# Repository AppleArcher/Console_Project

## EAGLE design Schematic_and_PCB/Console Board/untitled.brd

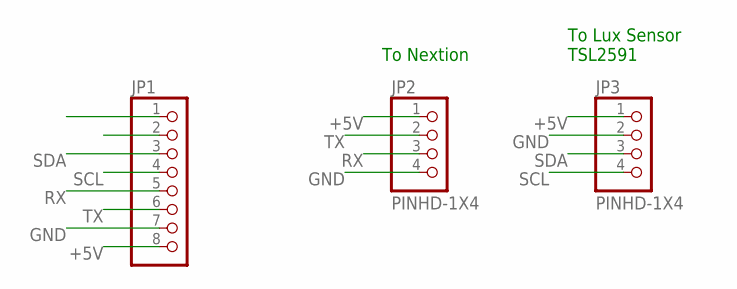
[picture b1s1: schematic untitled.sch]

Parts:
JP1: PINHD-1X8BIG; 1X08-BIG
JP2, JP3: PINHD-1X4; 1X04

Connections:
+5V: JP1.8, JP2.1, JP3.1
GND: JP1.7, JP2.4, JP3.2
RX: JP1.5, JP2.3
SCL: JP1.4, JP3.4
SDA: JP1.3, JP3.3
TX: JP1.6, JP2.2

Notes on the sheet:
To Nextion
To Lux Sensor TSL2591

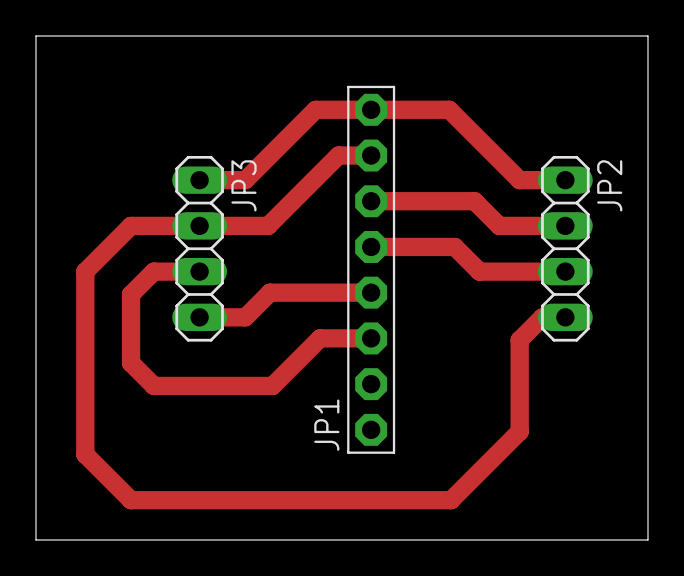
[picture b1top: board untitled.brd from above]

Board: 2 copper layers, 34.0 x 28.0 mm, 3 parts (0 on the bottom side), 6 nets.

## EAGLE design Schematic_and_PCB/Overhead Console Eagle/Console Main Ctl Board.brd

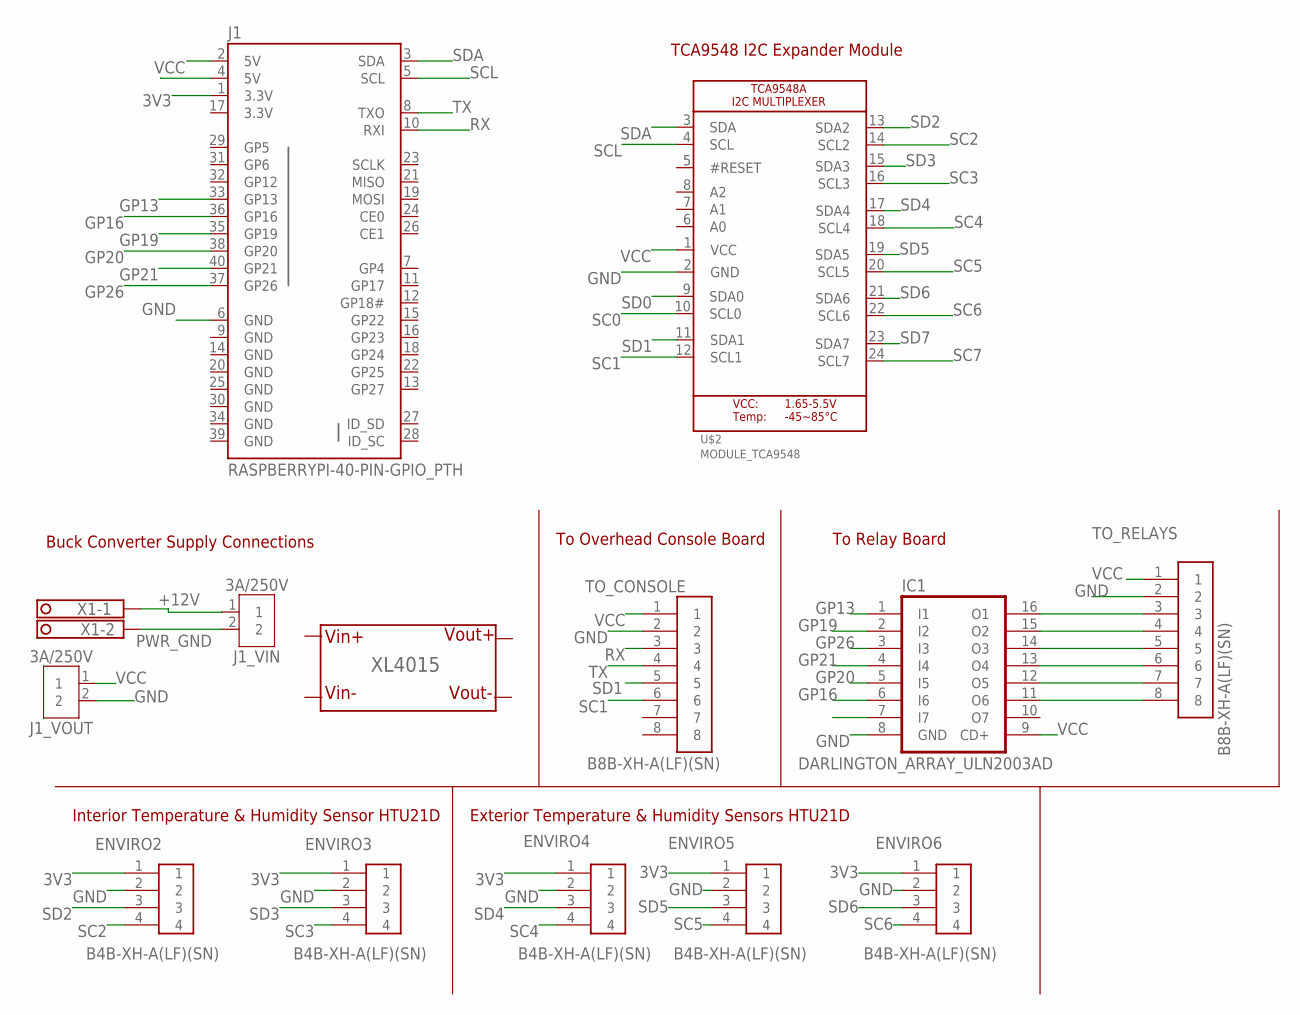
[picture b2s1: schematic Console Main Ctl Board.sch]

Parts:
ENVIRO2, ENVIRO3, ENVIRO4, ENVIRO5, ENVIRO6: B4B-XH-A(LF)(SN)
IC1: DARLINGTON_ARRAY_ULN2003AD; SO16
J1: RASPBERRYPI-40-PIN-GPIO_PTH; 2X20_SHROUDED
J1_VIN, J1_VOUT: 3A/250V; B2B-XH-A
TO_CONSOLE: B8B-XH-A(LF)(SN)
TO_RELAYS: B8B-XH-A(LF)(SN)
U$1: XL4015-MODULE
U$2: MODULE_TCA9548; MODULE_TCA9548A
X1: TERMINAL-BLOCK-3.5MM-2-PIN-LONG-PAD; TERMINAL-BLOCK-2-PIN-3.5MM-LONG-PAD

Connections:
3.3V: J1.17 (3.3V)
3V3: ENVIRO2.1, ENVIRO3.1, ENVIRO4.1, ENVIRO5.1, ENVIRO6.1, J1.1 (3.3V)
+12V: J1_VIN.1, X1.1
GND: ENVIRO2.2, ENVIRO3.2, ENVIRO4.2, ENVIRO5.2, ENVIRO6.2, IC1.8 (GND), J1.6 (GND), J1.9 (GND), J1.14 (GND), J1.20 (GND), J1.25 (GND), J1.30 (GND), J1.34 (GND), J1.39 (GND), J1_VOUT.2, TO_CONSOLE.2, TO_RELAYS.2, U$2.2 (GND)
GP13: IC1.1 (I1), J1.33 (GP13)
GP16: IC1.6 (I6), J1.36 (GP16)
GP19: IC1.2 (I2), J1.35 (GP19)
GP20: IC1.5 (I5), J1.38 (GP20)
GP21: IC1.4 (I4), J1.40 (GP21)
GP26: IC1.3 (I3), J1.37 (GP26)
unnamed: IC1.16 (O1), TO_RELAYS.3
unnamed: IC1.15 (O2), TO_RELAYS.4
unnamed: IC1.14 (O3), TO_RELAYS.5
unnamed: IC1.13 (O4), TO_RELAYS.6
unnamed: IC1.12 (O5), TO_RELAYS.7
unnamed: IC1.11 (O6), TO_RELAYS.8
PWR_GND: J1_VIN.2, X1.2
RX: J1.10 (RXI), TO_CONSOLE.3
SC0: U$2.10 (SCL0)
SC1: TO_CONSOLE.6, U$2.12 (SCL1)
SC2: ENVIRO2.4, U$2.14 (SCL2)
SC3: ENVIRO3.4, U$2.16 (SCL3)
SC4: ENVIRO4.4, U$2.18 (SCL4)
SC5: ENVIRO5.4, U$2.20 (SCL5)
SC6: ENVIRO6.4, U$2.22 (SCL6)
SC7: U$2.24 (SCL7)
SCL: J1.5 (SCL), U$2.4 (SCL)
SD0: U$2.9 (SDA0)
SD1: TO_CONSOLE.5, U$2.11 (SDA1)
SD2: ENVIRO2.3, U$2.13 (SDA2)
SD3: ENVIRO3.3, U$2.15 (SDA3)
SD4: ENVIRO4.3, U$2.17 (SDA4)
SD5: ENVIRO5.3, U$2.19 (SDA5)
SD6: ENVIRO6.3, U$2.21 (SDA6)
SD7: U$2.23 (SDA7)
SDA: J1.3 (SDA), U$2.3 (SDA)
TX: J1.8 (TXO), TO_CONSOLE.4
VCC: IC1.9 (CD+), J1.2 (5V), J1_VOUT.1, TO_CONSOLE.1, TO_RELAYS.1, U$2.1 (VCC)

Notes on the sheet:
To Overhead Console Board
To Relay Board
TCA9548 I2C Expander Module
Interior Temperature & Humidity Sensor HTU21D
Exterior Temperature & Humidity Sensors HTU21D
Buck Converter Supply Connections

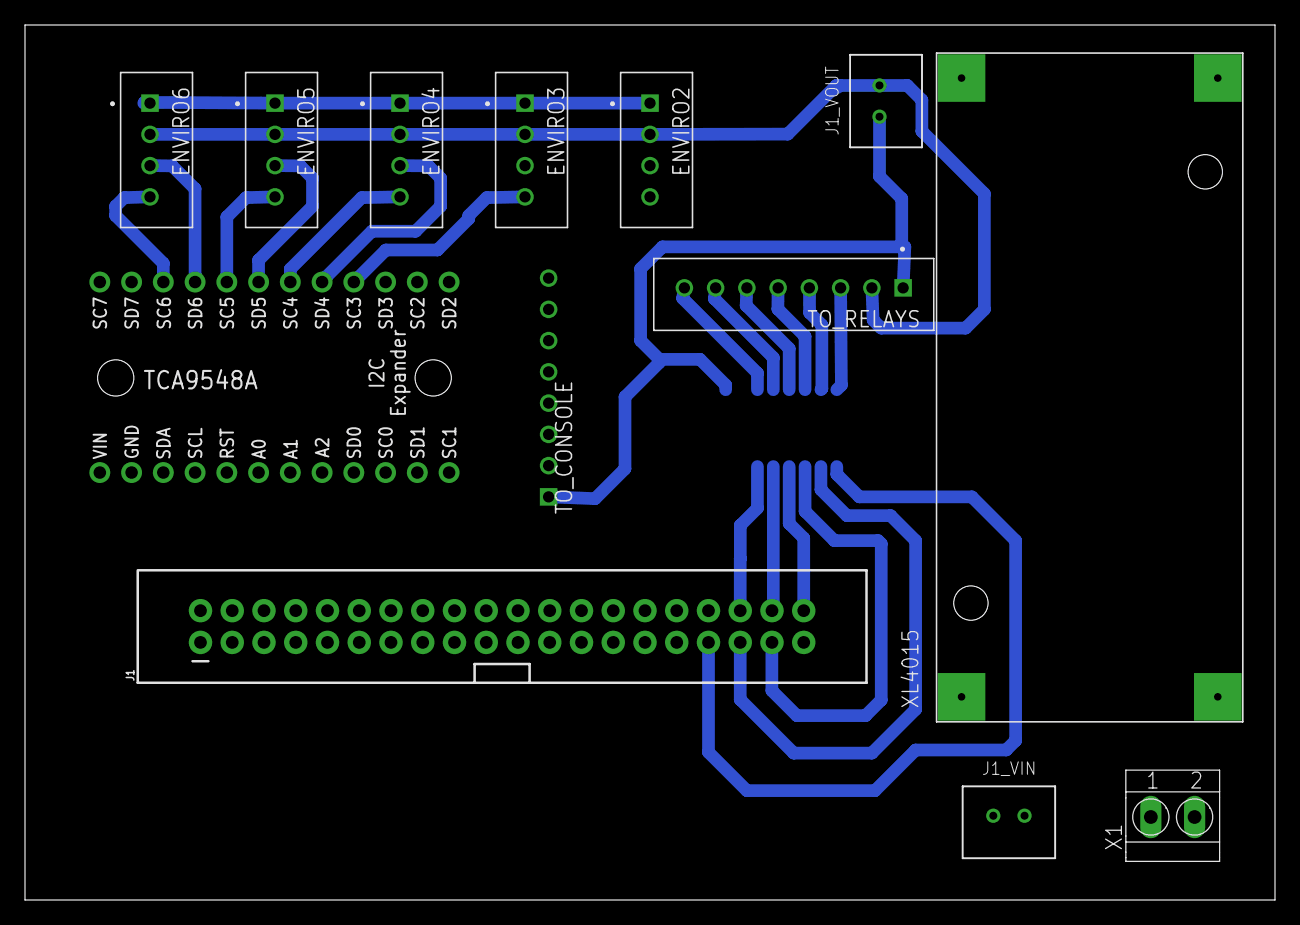
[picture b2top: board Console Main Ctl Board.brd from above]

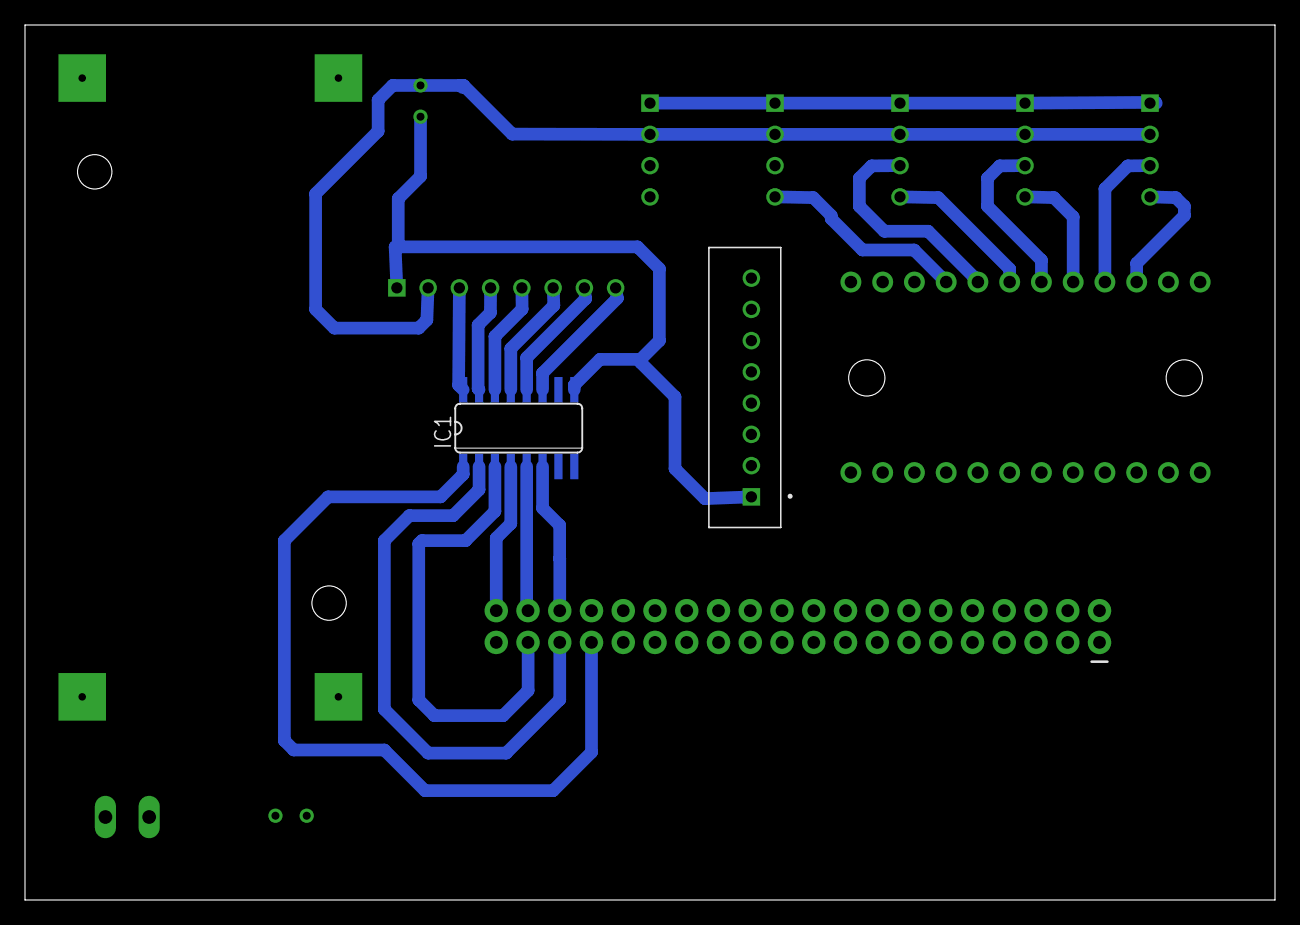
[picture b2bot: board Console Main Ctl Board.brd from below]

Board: 2 copper layers, 100.0 x 70.0 mm, 14 parts (2 on the bottom side), 33 nets.

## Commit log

2021-07-11 Sensor Class Work In Progress
2021-12-04 First full project commit.
2021-12-04 Nextion Project Files
2021-12-04 Schematics and Pcbs

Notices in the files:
parts and their libraries:
SparkFun-Connectors: Licensing: Creative Commons ShareAlike 4.0 International - https://creativecommons.org/licenses/by-sa/4.0
